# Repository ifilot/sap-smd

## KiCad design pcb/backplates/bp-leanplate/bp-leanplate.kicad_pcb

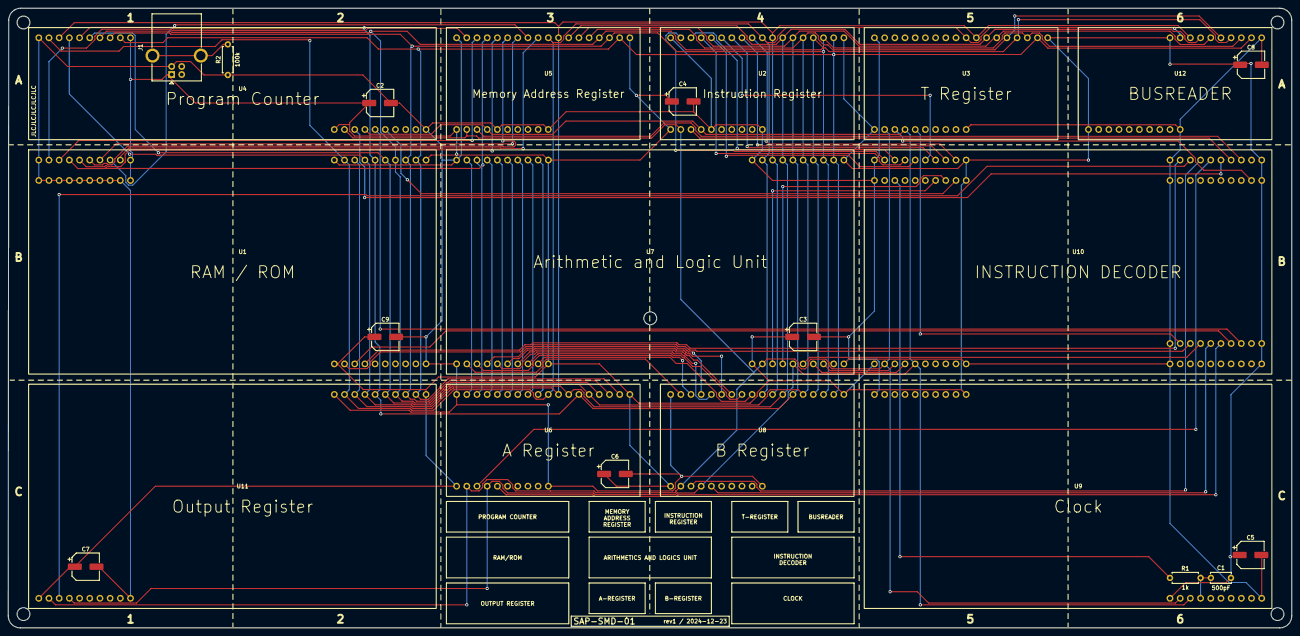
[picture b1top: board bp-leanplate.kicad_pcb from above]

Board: 2 copper layers, 319.9 x 154.4 mm, 29 parts (0 on the bottom side), 67 nets.

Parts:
C1: 500pF; C_Disc_D5.0mm_W2.5mm_P5.00mm
C2: 10uF; CP_Elec_6.3x3.9
C3, C4, C5, C6, C7, C8, C9: 220uF; CP_Elec_6.3x3.9
H1, H2, H3, H4, H5: MountingHole; MountingHole_3.2mm_M3
J1: USB_B; USB_B_OST_USB-B1HSxx_Horizontal
R1: 1k; R_Axial_DIN0207_L6.3mm_D2.5mm_P7.62mm_Horizontal
R2: 100k; R_Axial_DIN0207_L6.3mm_D2.5mm_P7.62mm_Horizontal
U1: RAM / ROM; sap-ramrom
U2: Instruction Register; sap-gpr-halfsize
U3: T Register; sap-gpr-halfsize
U4: Program Counter; sap-pc
U5: Memory Address Register; sap-gpr-halfsize
U6: A Register; sap-gpr-halfsize
U7: Arithmetic and Logic Unit; sap-alu
U8: B Register; sap-gpr-halfsize
U9: Clock; sap-clock
U10: INSTRUCTION DECODER; sap-id
U11: Output Register; sap-output
U12: BUSREADER; sap-busreader

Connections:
AI: U6.19 (IN), U10.13 (OCRA4)
AO: U6.21 (OUT), U10.28 (OCRB3)
A_D0: U6.9 (L0), U7.9 (A0)
A_D1: U6.10 (L1), U7.10 (A1)
A_D2: U6.11 (L2), U7.11 (A2)
A_D3: U6.12 (L3), U7.12 (A3)
A_D4: U6.13 (L4), U7.13 (A4)
A_D5: U6.14 (L5), U7.14 (A5)
A_D6: U6.15 (L6), U7.15 (A6)
A_D7: U6.16 (L7), U7.16 (A7)
BI: U8.19 (IN), U10.14 (OCRA5)
BO: U8.21 (OUT), U10.29 (OCRB4)
BUS0: U1.1 (BUS0), U2.1 (BUS0), U3.1 (BUS0), U4.1 (BUS0), U5.1 (BUS0), U6.1 (BUS0), U7.1 (BUS0), U8.1 (BUS0), U11.1 (BUS0), U12.1 (BUS0)
BUS1: U1.2 (BUS1), U2.2 (BUS1), U3.2 (BUS1), U4.2 (BUS1), U5.2 (BUS1), U6.2 (BUS1), U7.2 (BUS1), U8.2 (BUS1), U11.2 (BUS1), U12.2 (BUS1)
BUS2: U1.3 (BUS2), U2.3 (BUS2), U3.3 (BUS2), U4.3 (BUS2), U5.3 (BUS2), U6.3 (BUS2), U7.3 (BUS2), U8.3 (BUS2), U11.3 (BUS2), U12.3 (BUS2)
BUS3: U1.4 (BUS3), U2.4 (BUS3), U3.4 (BUS3), U4.4 (BUS3), U5.4 (BUS3), U6.4 (BUS3), U7.4 (BUS3), U8.4 (BUS3), U11.4 (BUS3), U12.4 (BUS3)
BUS4: U1.5 (BUS4), U2.5 (BUS4), U3.5 (BUS4), U4.5 (BUS4), U5.5 (BUS4), U6.5 (BUS4), U7.5 (BUS4), U8.5 (BUS4), U11.5 (BUS4), U12.5 (BUS4)
BUS5: U1.6 (BUS5), U2.6 (BUS5), U3.6 (BUS5), U4.6 (BUS5), U5.6 (BUS5), U6.6 (BUS5), U7.6 (BUS5), U8.6 (BUS5), U11.6 (BUS5), U12.6 (BUS5)
BUS6: U1.7 (BUS6), U2.7 (BUS6), U3.7 (BUS6), U4.7 (BUS6), U5.7 (BUS6), U6.7 (BUS6), U7.7 (BUS6), U8.7 (BUS6), U11.7 (BUS6), U12.7 (BUS6)
BUS7: U1.8 (BUS7), U2.8 (BUS7), U3.8 (BUS7), U4.8 (BUS7), U5.8 (BUS7), U6.8 (BUS7), U7.8 (BUS7), U8.8 (BUS7), U11.8 (BUS7), U12.8 (BUS7)
B_D0: U7.17 (B0), U8.9 (L0)
B_D1: U7.18 (B1), U8.10 (L1)
B_D2: U7.19 (B2), U8.11 (L2)
B_D3: U7.20 (B3), U8.12 (L3)
B_D4: U7.21 (B4), U8.13 (L4)
B_D5: U7.22 (B5), U8.14 (L5)
B_D6: U7.23 (B6), U8.15 (L6)
B_D7: U7.24 (B7), U8.16 (L7)
CE: U4.14 (CE), U10.41 (PCL0)
CF: U7.31 (CF), U10.52 (CF)
CLK: U2.18 (CLK), U3.18 (CLK), U4.10 (CLK), U5.18 (CLK), U6.18 (CLK), U7.26 (CLK), U8.18 (CLK), U9.2 (CLK), U10.50 (CLK), U11.10 (CLK)
CO: U4.13 (CO), U10.26 (OCRB1)
EO: U7.30 (EO), U10.30 (OCRB5)
FI: U7.28 (FI), U10.42 (PCL1)
GND: C2.2, C3.2, C4.2, C5.2, C6.2, C7.2, C8.2, C9.2, J1.4 (GND), R2.1, U1.17 (L8), U1.18 (L9), U1.19 (L10), U1.20 (L11), U1.21 (L12), U1.22 (L13), U1.23 (L14), U1.24 (L15), U1.29 (GND), U2.21 (OUT), U2.22 (GND), U3.22 (GND), U4.15 (GND), U5.21 (OUT), U5.22 (GND), U6.22 (GND), U7.33 (GND), U8.22 (GND), U9.5 (GND), U10.54 (GND), U11.13 (GND), U12.10 (GND)
HLT: R1.1, U10.47 (PCL6)
HLTIN: C1.1, R1.2, U9.4 (HLT)
II: U2.19 (IN), U10.11 (OCRA2)
IR_D0: U2.9 (L0), U10.1 (I0)
IR_D1: U2.10 (L1), U10.2 (I1)
IR_D2: U2.11 (L2), U10.3 (I2)
IR_D3: U2.12 (L3), U10.4 (I3)
IR_D4: U2.13 (L4), U10.5 (I4)
IR_D5: U2.14 (L5), U10.6 (I5)
IR_D6: U2.15 (L6), U10.7 (I6)
IR_D7: U2.16 (L7), U10.8 (I7)
J: U4.11 (J), U10.12 (OCRA3)
MAR_A0: U1.9 (L0), U5.9 (L0)
MAR_A1: U1.10 (L1), U5.10 (L1)
MAR_A2: U1.11 (L2), U5.11 (L2)
MAR_A3: U1.12 (L3), U5.12 (L3)
MAR_A4: U1.13 (L4), U5.13 (L4)
MAR_A5: U1.14 (L5), U5.14 (L5)
MAR_A6: U1.15 (L6), U5.15 (L6)
MAR_A7: U1.16 (L7), U5.16 (L7)
MI: U5.19 (IN), U10.10 (OCRA1)
unnamed: J1.5 (Shield), R2.2
OI: U10.15 (OCRA6), U11.11 (IN)
PCL2: U7.27 (SU), U10.43 (PCL2)
RI: U1.28 (RI), U10.16 (OCRA7)
RO: U1.26 (RO), U10.31 (OCRB6)
RRO: U1.27 (RRO), U10.27 (OCRB2)
TI: U3.19 (IN), U10.17 (OCRA8)
TO: U3.21 (OUT), U10.32 (OCRB7)
VCC: C1.2, C2.1, C3.1, C4.1, C5.1, C6.1, C7.1, C8.1, C9.1, J1.1 (VBUS), U1.25 (VCC), U2.17 (VCC), U3.17 (VCC), U4.9 (VCC), U5.17 (VCC), U6.17 (VCC), U7.25 (VCC), U8.17 (VCC), U9.1 (VCC), U10.49 (VCC), U11.9 (VCC), U12.9 (VCC)
ZF: U7.32 (ZF), U10.51 (ZF)
~CLR: U2.20 (~CLR), U3.20 (~CLR), U4.12 (~CLR), U5.20 (~CLR), U6.20 (~CLR), U7.29 (CLR), U8.20 (~CLR), U9.3 (~CLR), U10.53 (~CLR), U11.12 (~CLR)

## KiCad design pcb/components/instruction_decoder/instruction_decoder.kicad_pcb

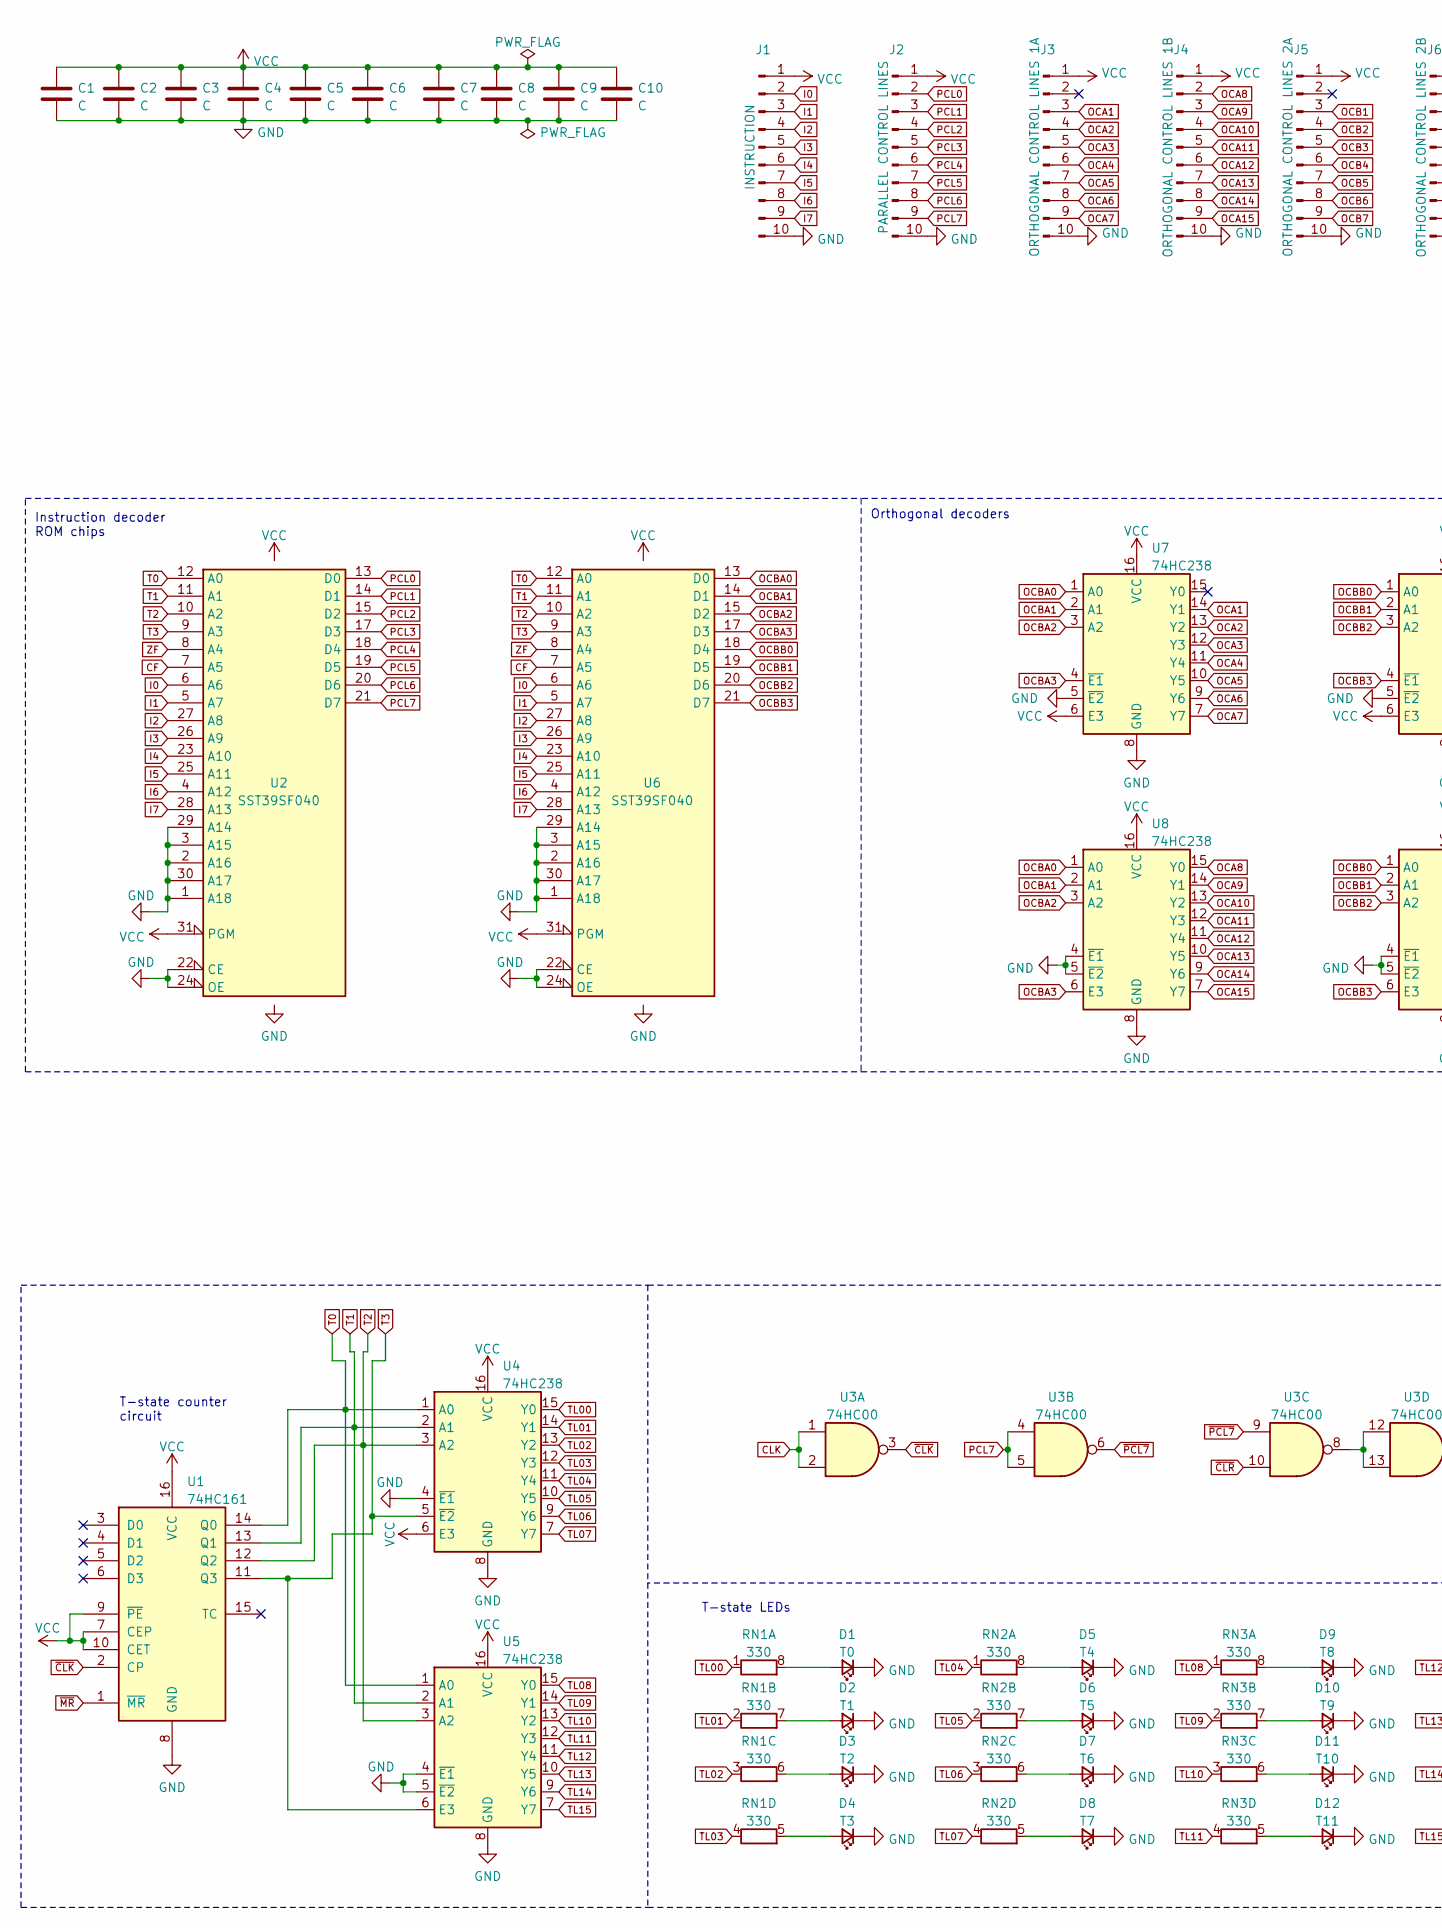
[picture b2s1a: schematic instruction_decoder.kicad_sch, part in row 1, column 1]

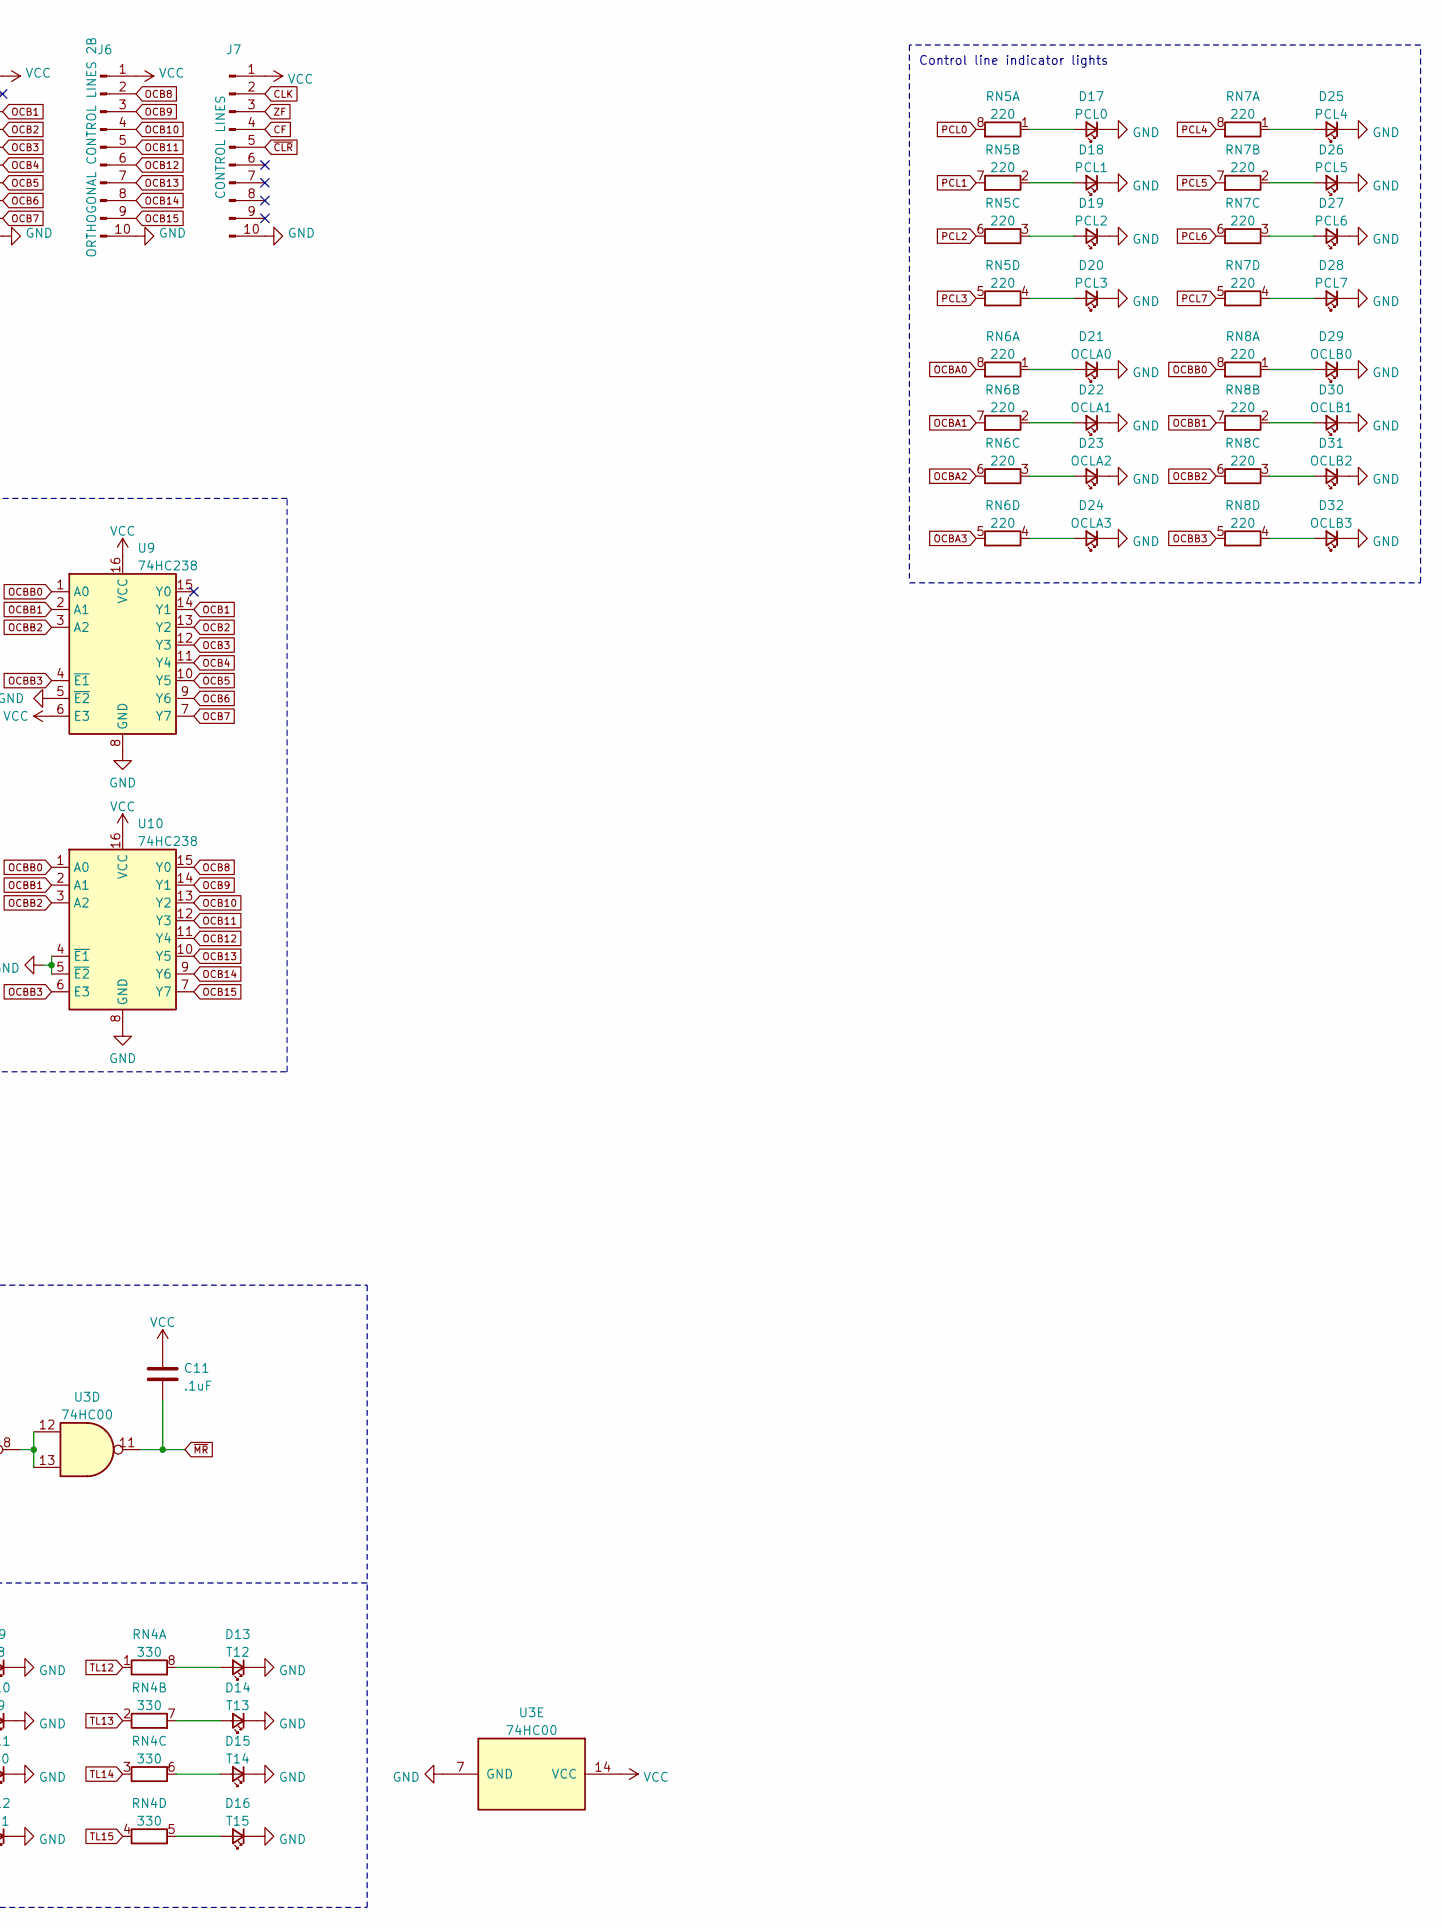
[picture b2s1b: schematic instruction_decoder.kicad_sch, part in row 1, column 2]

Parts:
C1, C2, C3, C4, C5, C6, C7, C8, C9, C10: C; C_0805_2012Metric
C11: .1uF; C_Disc_D5.0mm_W2.5mm_P5.00mm
D1: T0; LED_0805_2012Metric
D2: T1; LED_0805_2012Metric
D3: T2; LED_0805_2012Metric
D4: T3; LED_0805_2012Metric
D5: T4; LED_0805_2012Metric
D6: T5; LED_0805_2012Metric
D7: T6; LED_0805_2012Metric
D8: T7; LED_0805_2012Metric
D9: T8; LED_0805_2012Metric
D10: T9; LED_0805_2012Metric
D11: T10; LED_0805_2012Metric
D12: T11; LED_0805_2012Metric
D13: T12; LED_0805_2012Metric
D14: T13; LED_0805_2012Metric
D15: T14; LED_0805_2012Metric
D16: T15; LED_0805_2012Metric
D17: PCL0; LED_0805_2012Metric
D18: PCL1; LED_0805_2012Metric
D19: PCL2; LED_0805_2012Metric
D20: PCL3; LED_0805_2012Metric
D21: OCLA0; LED_0805_2012Metric
D22: OCLA1; LED_0805_2012Metric
D23: OCLA2; LED_0805_2012Metric
D24: OCLA3; LED_0805_2012Metric
D25: PCL4; LED_0805_2012Metric
D26: PCL5; LED_0805_2012Metric
D27: PCL6; LED_0805_2012Metric
D28: PCL7; LED_0805_2012Metric
D29: OCLB0; LED_0805_2012Metric
D30: OCLB1; LED_0805_2012Metric
D31: OCLB2; LED_0805_2012Metric
D32: OCLB3; LED_0805_2012Metric
J1: INSTRUCTION; PinHeader_1x10_P2.54mm_Vertical
J2: PARALLEL CONTROL LINES; PinHeader_1x10_P2.54mm_Vertical
J3: ORTHOGONAL CONTROL LINES 1A; PinHeader_1x10_P2.54mm_Vertical
J4: ORTHOGONAL CONTROL LINES 1B; PinHeader_1x10_P2.54mm_Vertical
J5: ORTHOGONAL CONTROL LINES 2A; PinHeader_1x10_P2.54mm_Vertical
J6: ORTHOGONAL CONTROL LINES 2B; PinHeader_1x10_P2.54mm_Vertical
J7: CONTROL LINES; PinHeader_1x10_P2.54mm_Vertical
RN1, RN2, RN3, RN4: 330; R_Array_Convex_4x0603
RN5, RN6, RN7, RN8: 220; R_Array_Convex_4x0603
U1: 74HC161; SO-16_3.9x9.9mm_P1.27mm
U2, U6: SST39SF040; PLCC-32_THT-Socket
U3: 74HC00; SO-14_3.9x8.65mm_P1.27mm
U4, U5, U7, U8, U9, U10: 74HC238; SO-16_3.9x9.9mm_P1.27mm

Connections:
CF: J7.4, U2.7 (A5), U6.7 (A5)
CLK: J7.2, U3.1, U3.2
GND: C1.2, C2.2, C3.2, C4.2, C5.2, C6.2, C7.2, C8.2, C9.2, C10.2, D1.1 (K), D2.1 (K), D3.1 (K), D4.1 (K), D5.1 (K), D6.1 (K), D7.1 (K), D8.1 (K), D9.1 (K), D10.1 (K), D11.1 (K), D12.1 (K), D13.1 (K), D14.1 (K), D15.1 (K), D16.1 (K), D17.1 (K), D18.1 (K), D19.1 (K), D20.1 (K), D21.1 (K), D22.1 (K), D23.1 (K), D24.1 (K), D25.1 (K), D26.1 (K), D27.1 (K), D28.1 (K), D29.1 (K), D30.1 (K), D31.1 (K), D32.1 (K), J1.10, J2.10, J3.10, J4.10, J5.10, J6.10, J7.10, U1.8 (GND), U2.1 (A18), U2.2 (A16), U2.3 (A15), U2.16 (GND), U2.22 (CE), U2.24 (OE), U2.29 (A14), U2.30 (A17), U3.7 (GND), U4.4 (~E1), U4.8 (GND), U5.4 (~E1), U5.5 (~E2), U5.8 (GND), U6.1 (A18), U6.2 (A16), U6.3 (A15), U6.16 (GND), U6.22 (CE), U6.24 (OE), U6.29 (A14), U6.30 (A17), U7.5 (~E2), U7.8 (GND), U8.4 (~E1), U8.5 (~E2), U8.8 (GND), U9.5 (~E2), U9.8 (GND), U10.4 (~E1), U10.5 (~E2), U10.8 (GND)
I0: J1.2, U2.6 (A6), U6.6 (A6)
I1: J1.3, U2.5 (A7), U6.5 (A7)
I2: J1.4, U2.27 (A8), U6.27 (A8)
I3: J1.5, U2.26 (A9), U6.26 (A9)
I4: J1.6, U2.23 (A10), U6.23 (A10)
I5: J1.7, U2.25 (A11), U6.25 (A11)
I6: J1.8, U2.4 (A12), U6.4 (A12)
I7: J1.9, U2.28 (A13), U6.28 (A13)
unnamed: D1.2 (A), RN1.8 (R1.2)
unnamed: D2.2 (A), RN1.7 (R2.2)
unnamed: D3.2 (A), RN1.6 (R3.2)
unnamed: D4.2 (A), RN1.5 (R4.2)
unnamed: D5.2 (A), RN2.8 (R1.2)
unnamed: D6.2 (A), RN2.7 (R2.2)
unnamed: D7.2 (A), RN2.6 (R3.2)
unnamed: D8.2 (A), RN2.5 (R4.2)
unnamed: D9.2 (A), RN3.8 (R1.2)
unnamed: D10.2 (A), RN3.7 (R2.2)
unnamed: D11.2 (A), RN3.6 (R3.2)
unnamed: D12.2 (A), RN3.5 (R4.2)
unnamed: D13.2 (A), RN4.8 (R1.2)
unnamed: D14.2 (A), RN4.7 (R2.2)
unnamed: D15.2 (A), RN4.6 (R3.2)
unnamed: D16.2 (A), RN4.5 (R4.2)
unnamed: D17.2 (A), RN5.1 (R1.1)
unnamed: D18.2 (A), RN5.2 (R2.1)
unnamed: D19.2 (A), RN5.3 (R3.1)
unnamed: D20.2 (A), RN5.4 (R4.1)
unnamed: D21.2 (A), RN6.1 (R1.1)
unnamed: D22.2 (A), RN6.2 (R2.1)
unnamed: D23.2 (A), RN6.3 (R3.1)
unnamed: D24.2 (A), RN6.4 (R4.1)
unnamed: D25.2 (A), RN7.1 (R1.1)
unnamed: D26.2 (A), RN7.2 (R2.1)
unnamed: D27.2 (A), RN7.3 (R3.1)
unnamed: D28.2 (A), RN7.4 (R4.1)
unnamed: D29.2 (A), RN8.1 (R1.1)
unnamed: D30.2 (A), RN8.2 (R2.1)
unnamed: D31.2 (A), RN8.3 (R3.1)
unnamed: D32.2 (A), RN8.4 (R4.1)
unnamed: U3.8, U3.12, U3.13
OCA1: J3.3, U7.14 (Y1)
OCA2: J3.4, U7.13 (Y2)
OCA3: J3.5, U7.12 (Y3)
OCA4: J3.6, U7.11 (Y4)
OCA5: J3.7, U7.10 (Y5)
OCA6: J3.8, U7.9 (Y6)
OCA7: J3.9, U7.7 (Y7)
OCA8: J4.2, U8.15 (Y0)
OCA9: J4.3, U8.14 (Y1)
OCA10: J4.4, U8.13 (Y2)
OCA11: J4.5, U8.12 (Y3)
OCA12: J4.6, U8.11 (Y4)
OCA13: J4.7, U8.10 (Y5)
OCA14: J4.8, U8.9 (Y6)
OCA15: J4.9, U8.7 (Y7)
OCB1: J5.3, U9.14 (Y1)
OCB2: J5.4, U9.13 (Y2)
OCB3: J5.5, U9.12 (Y3)
OCB4: J5.6, U9.11 (Y4)
OCB5: J5.7, U9.10 (Y5)
OCB6: J5.8, U9.9 (Y6)
OCB7: J5.9, U9.7 (Y7)
OCB8: J6.2, U10.15 (Y0)
OCB9: J6.3, U10.14 (Y1)
OCB10: J6.4, U10.13 (Y2)
OCB11: J6.5, U10.12 (Y3)
OCB12: J6.6, U10.11 (Y4)
OCB13: J6.7, U10.10 (Y5)
OCB14: J6.8, U10.9 (Y6)
OCB15: J6.9, U10.7 (Y7)
OCBA0: RN6.8 (R1.2), U6.13 (D0), U7.1 (A0), U8.1 (A0)
OCBA1: RN6.7 (R2.2), U6.14 (D1), U7.2 (A1), U8.2 (A1)
OCBA2: RN6.6 (R3.2), U6.15 (D2), U7.3 (A2), U8.3 (A2)
OCBA3: RN6.5 (R4.2), U6.17 (D3), U7.4 (~E1), U8.6 (E3)
OCBB0: RN8.8 (R1.2), U6.18 (D4), U9.1 (A0), U10.1 (A0)
OCBB1: RN8.7 (R2.2), U6.19 (D5), U9.2 (A1), U10.2 (A1)
OCBB2: RN8.6 (R3.2), U6.20 (D6), U9.3 (A2), U10.3 (A2)
OCBB3: RN8.5 (R4.2), U6.21 (D7), U9.4 (~E1), U10.6 (E3)
PCL0: J2.2, RN5.8 (R1.2), U2.13 (D0)
PCL1: J2.3, RN5.7 (R2.2), U2.14 (D1)
PCL2: J2.4, RN5.6 (R3.2), U2.15 (D2)
PCL3: J2.5, RN5.5 (R4.2), U2.17 (D3)
PCL4: J2.6, RN7.8 (R1.2), U2.18 (D4)
PCL5: J2.7, RN7.7 (R2.2), U2.19 (D5)
PCL6: J2.8, RN7.6 (R3.2), U2.20 (D6)
PCL7: J2.9, RN7.5 (R4.2), U2.21 (D7), U3.4, U3.5
T0: U1.14 (Q0), U2.12 (A0), U4.1 (A0), U5.1 (A0), U6.12 (A0)
T1: U1.13 (Q1), U2.11 (A1), U4.2 (A1), U5.2 (A1), U6.11 (A1)
T2: U1.12 (Q2), U2.10 (A2), U4.3 (A2), U5.3 (A2), U6.10 (A2)
T3: U1.11 (Q3), U2.9 (A3), U4.5 (~E2), U5.6 (E3), U6.9 (A3)
TL00: RN1.1 (R1.1), U4.15 (Y0)
TL01: RN1.2 (R2.1), U4.14 (Y1)
TL02: RN1.3 (R3.1), U4.13 (Y2)
TL03: RN1.4 (R4.1), U4.12 (Y3)
TL04: RN2.1 (R1.1), U4.11 (Y4)
TL05: RN2.2 (R2.1), U4.10 (Y5)
TL06: RN2.3 (R3.1), U4.9 (Y6)
TL07: RN2.4 (R4.1), U4.7 (Y7)
TL08: RN3.1 (R1.1), U5.15 (Y0)
TL09: RN3.2 (R2.1), U5.14 (Y1)
TL10: RN3.3 (R3.1), U5.13 (Y2)
TL11: RN3.4 (R4.1), U5.12 (Y3)
TL12: RN4.1 (R1.1), U5.11 (Y4)
TL13: RN4.2 (R2.1), U5.10 (Y5)
TL14: RN4.3 (R3.1), U5.9 (Y6)
TL15: RN4.4 (R4.1), U5.7 (Y7)
VCC: C1.1, C2.1, C3.1, C4.1, C5.1, C6.1, C7.1, C8.1, C9.1, C10.1, C11.1, J1.1, J2.1, J3.1, J4.1, J5.1, J6.1, J7.1, U1.7 (CEP), U1.9 (~PE), U1.10 (CET), U1.16 (VCC), U2.31 (PGM), U2.32 (VCC), U3.14 (VCC), U4.6 (E3), U4.16 (VCC), U5.16 (VCC), U6.31 (PGM), U6.32 (VCC), U7.6 (E3), U7.16 (VCC), U8.16 (VCC), U9.6 (E3), U9.16 (VCC), U10.16 (VCC)
ZF: J7.3, U2.8 (A4), U6.8 (A4)
~CLK: U1.2 (CP), U3.3
~CLR: J7.5, U3.10
~MR: C11.2, U1.1 (~MR), U3.11
~PCL7: U3.6, U3.9

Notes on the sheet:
T-state counter circuit
Orthogonal decoders
T-state LEDs
Instruction decoder ROM chips
Control line indicator lights

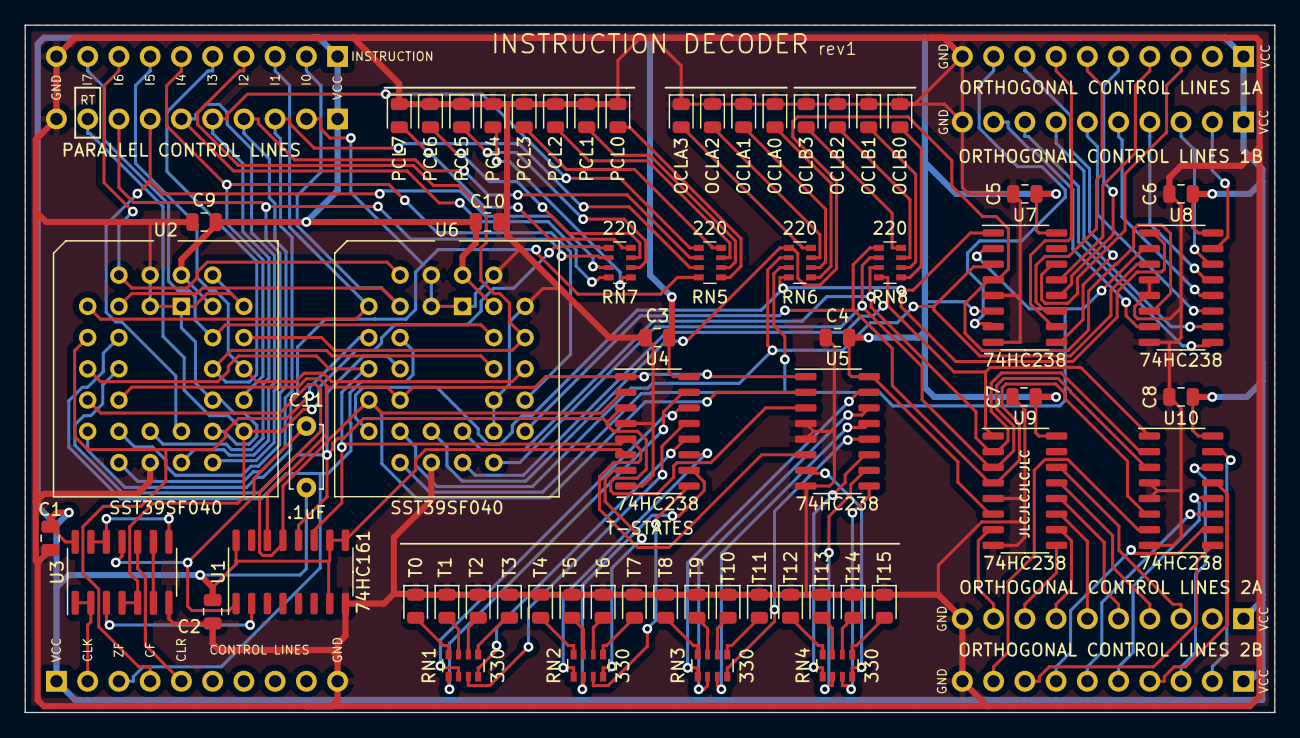
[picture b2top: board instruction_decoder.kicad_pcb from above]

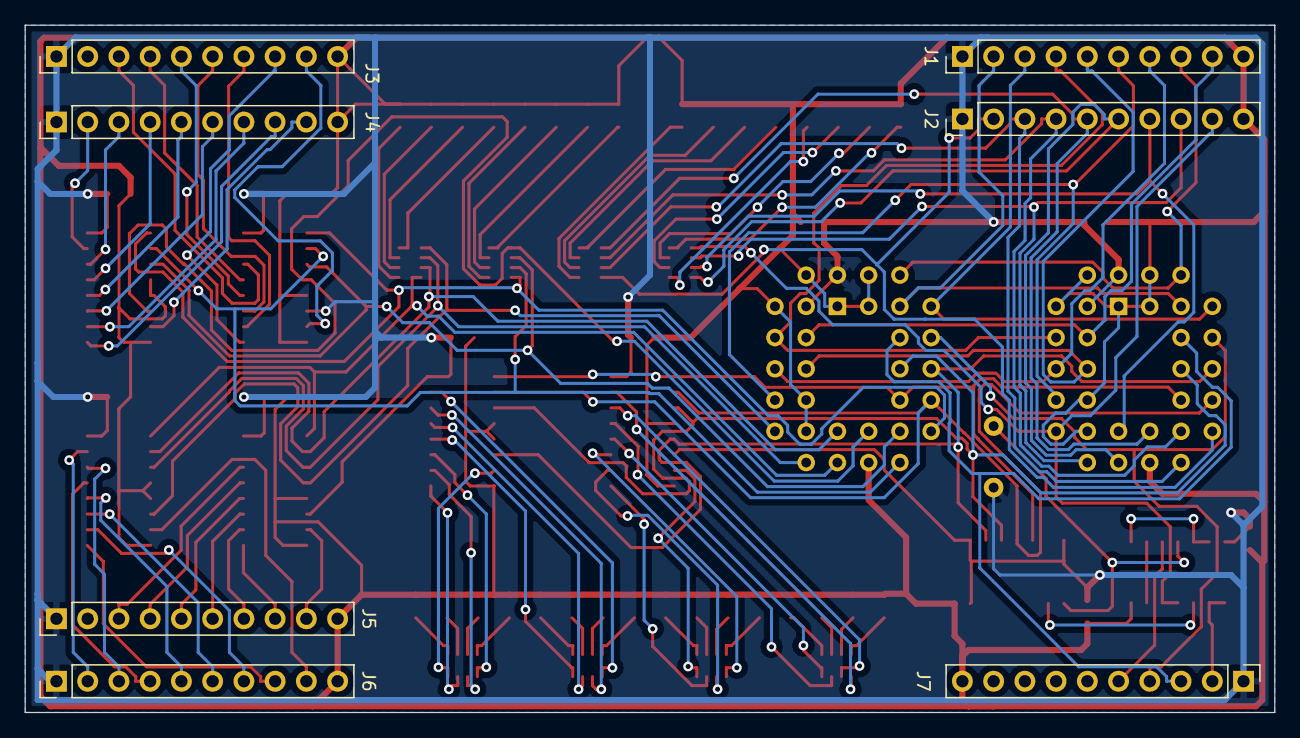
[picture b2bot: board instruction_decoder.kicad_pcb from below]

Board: 2 copper layers, 101.6 x 55.9 mm, 68 parts (7 on the bottom side), 116 nets.

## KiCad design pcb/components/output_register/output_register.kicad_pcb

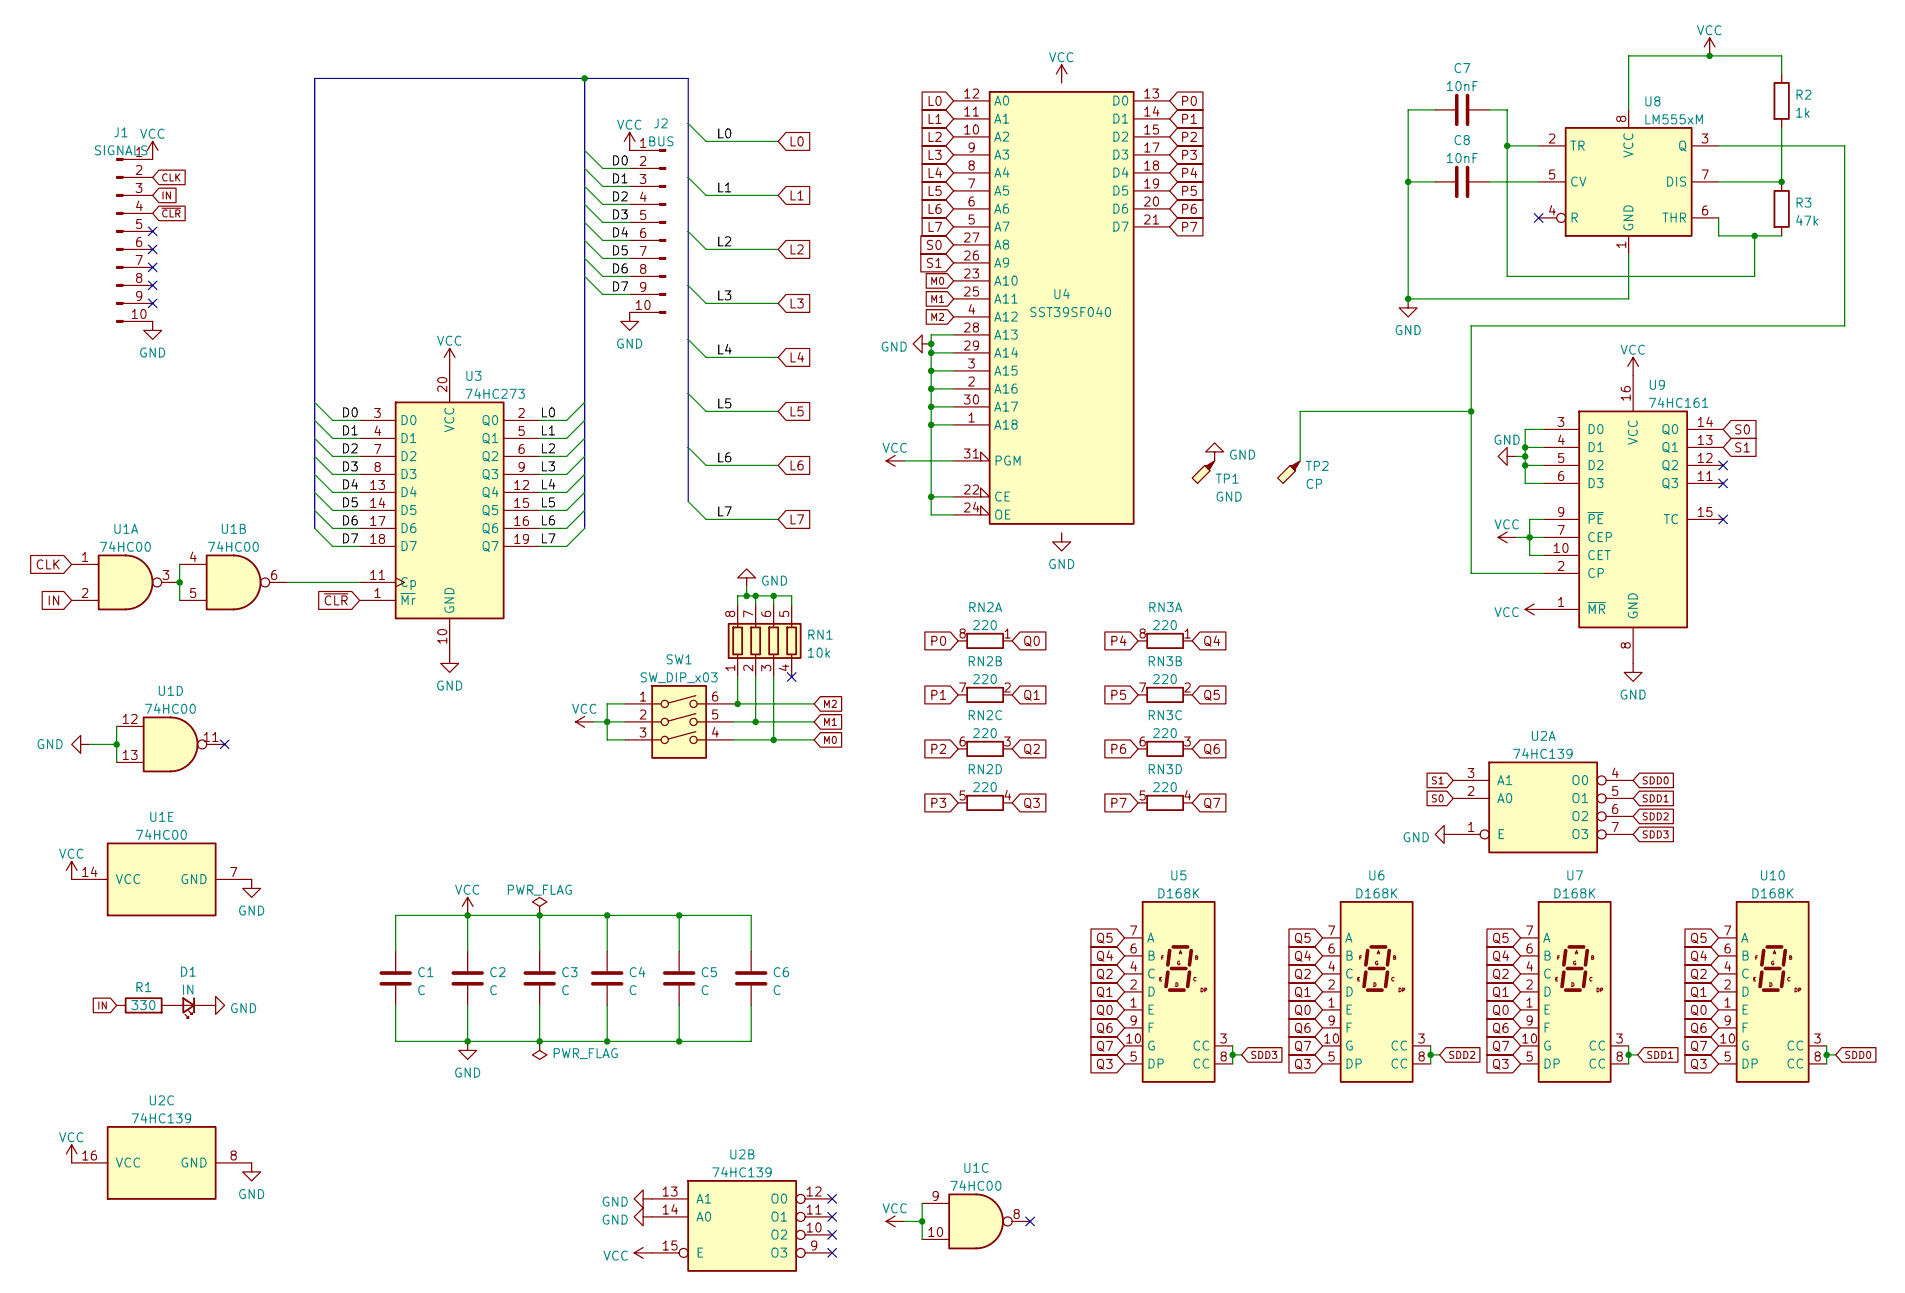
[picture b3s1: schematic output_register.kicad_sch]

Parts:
C1, C2, C3, C4, C5, C6: C; C_0805_2012Metric
C7, C8: 10nF; C_0805_2012Metric
D1: IN; LED_0805_2012Metric
J1: SIGNALS; PinHeader_1x10_P2.54mm_Vertical
J2: BUS; PinHeader_1x10_P2.54mm_Vertical
R1: 330; R_0805_2012Metric
R2: 1k; R_0805_2012Metric
R3: 47k; R_0805_2012Metric
RN1: 10k; R_Array_Convex_4x0603
RN2, RN3: 220; R_Array_Convex_4x0603
SW1: SW_DIP_x03; SW_DIP_SPSTx03_Slide_9.78x9.8mm_W7.62mm_P2.54mm
TP1: GND; TestPoint_THTPad_D2.0mm_Drill1.0mm
TP2: CP; TestPoint_THTPad_D2.0mm_Drill1.0mm
U1: 74HC00; SO-14_3.9x8.65mm_P1.27mm
U2: 74HC139; SO-16_3.9x9.9mm_P1.27mm
U3: 74HC273; SOIC-20W_7.5x12.8mm_P1.27mm
U4: SST39SF040; PLCC-32_THT-Socket
U5, U6, U7, U10: D168K; D1X8K
U8: LM555xM; SOIC-8_3.9x4.9mm_P1.27mm
U9: 74HC161; SO-16_3.9x9.9mm_P1.27mm

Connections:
/D0: J2.2, U3.3 (D0)
/D1: J2.3, U3.4 (D1)
/D2: J2.4, U3.7 (D2)
/D3: J2.5, U3.8 (D3)
/D4: J2.6, U3.13 (D4)
/D5: J2.7, U3.14 (D5)
/D6: J2.8, U3.17 (D6)
/D7: J2.9, U3.18 (D7)
CLK: J1.2, U1.1
GND: C1.2, C2.2, C3.2, C4.2, C5.2, C6.2, C7.1, C8.1, D1.1 (K), J1.10, J2.10, RN1.5 (R4.2), RN1.6 (R3.2), RN1.7 (R2.2), RN1.8 (R1.2), TP1.1, U1.7 (GND), U1.12, U1.13, U2.1 (E), U2.8 (GND), U2.13 (A1), U2.14 (A0), U3.10 (GND), U4.1 (A18), U4.2 (A16), U4.3 (A15), U4.16 (GND), U4.22 (CE), U4.24 (OE), U4.28 (A13), U4.29 (A14), U4.30 (A17), U8.1 (GND), U9.3 (D0), U9.4 (D1), U9.5 (D2), U9.6 (D3), U9.8 (GND)
IN: J1.3, R1.1, U1.2
L0: U3.2 (Q0), U4.12 (A0)
L1: U3.5 (Q1), U4.11 (A1)
L2: U3.6 (Q2), U4.10 (A2)
L3: U3.9 (Q3), U4.9 (A3)
L4: U3.12 (Q4), U4.8 (A4)
L5: U3.15 (Q5), U4.7 (A5)
L6: U3.16 (Q6), U4.6 (A6)
L7: U3.19 (Q7), U4.5 (A7)
M0: RN1.3 (R3.1), SW1.4, U4.23 (A10)
M1: RN1.2 (R2.1), SW1.5, U4.25 (A11)
M2: RN1.1 (R1.1), SW1.6, U4.4 (A12)
unnamed: C7.2, R3.2, U8.2 (TR), U8.6 (THR)
unnamed: C8.2, U8.5 (CV)
unnamed: D1.2 (A), R1.2
unnamed: R2.2, R3.1, U8.7 (DIS)
unnamed: U1.3, U1.4, U1.5
unnamed: U1.6, U3.11 (Cp)
unnamed: TP2.1, U8.3 (Q), U9.2 (CP)
P0: RN2.8 (R1.2), U4.13 (D0)
P1: RN2.7 (R2.2), U4.14 (D1)
P2: RN2.6 (R3.2), U4.15 (D2)
P3: RN2.5 (R4.2), U4.17 (D3)
P4: RN3.8 (R1.2), U4.18 (D4)
P5: RN3.7 (R2.2), U4.19 (D5)
P6: RN3.6 (R3.2), U4.20 (D6)
P7: RN3.5 (R4.2), U4.21 (D7)
Q0: RN2.1 (R1.1), U5.1 (E), U6.1 (E), U7.1 (E), U10.1 (E)
Q1: RN2.2 (R2.1), U5.2 (D), U6.2 (D), U7.2 (D), U10.2 (D)
Q2: RN2.3 (R3.1), U5.4 (C), U6.4 (C), U7.4 (C), U10.4 (C)
Q3: RN2.4 (R4.1), U5.5 (DP), U6.5 (DP), U7.5 (DP), U10.5 (DP)
Q4: RN3.1 (R1.1), U5.6 (B), U6.6 (B), U7.6 (B), U10.6 (B)
Q5: RN3.2 (R2.1), U5.7 (A), U6.7 (A), U7.7 (A), U10.7 (A)
Q6: RN3.3 (R3.1), U5.9 (F), U6.9 (F), U7.9 (F), U10.9 (F)
Q7: RN3.4 (R4.1), U5.10 (G), U6.10 (G), U7.10 (G), U10.10 (G)
S0: U2.2 (A0), U4.27 (A8), U9.14 (Q0)
S1: U2.3 (A1), U4.26 (A9), U9.13 (Q1)
SDD0: U2.4 (O0), U10.3 (CC), U10.8 (CC)
SDD1: U2.5 (O1), U7.3 (CC), U7.8 (CC)
SDD2: U2.6 (O2), U6.3 (CC), U6.8 (CC)
SDD3: U2.7 (O3), U5.3 (CC), U5.8 (CC)
VCC: C1.1, C2.1, C3.1, C4.1, C5.1, C6.1, J1.1, J2.1, R2.1, SW1.1, SW1.2, SW1.3, U1.9, U1.10, U1.14 (VCC), U2.15 (E), U2.16 (VCC), U3.20 (VCC), U4.31 (PGM), U4.32 (VCC), U8.8 (VCC), U9.1 (~MR), U9.7 (CEP), U9.9 (~PE), U9.10 (CET), U9.16 (VCC)
~CLR: J1.4, U3.1 (~Mr)

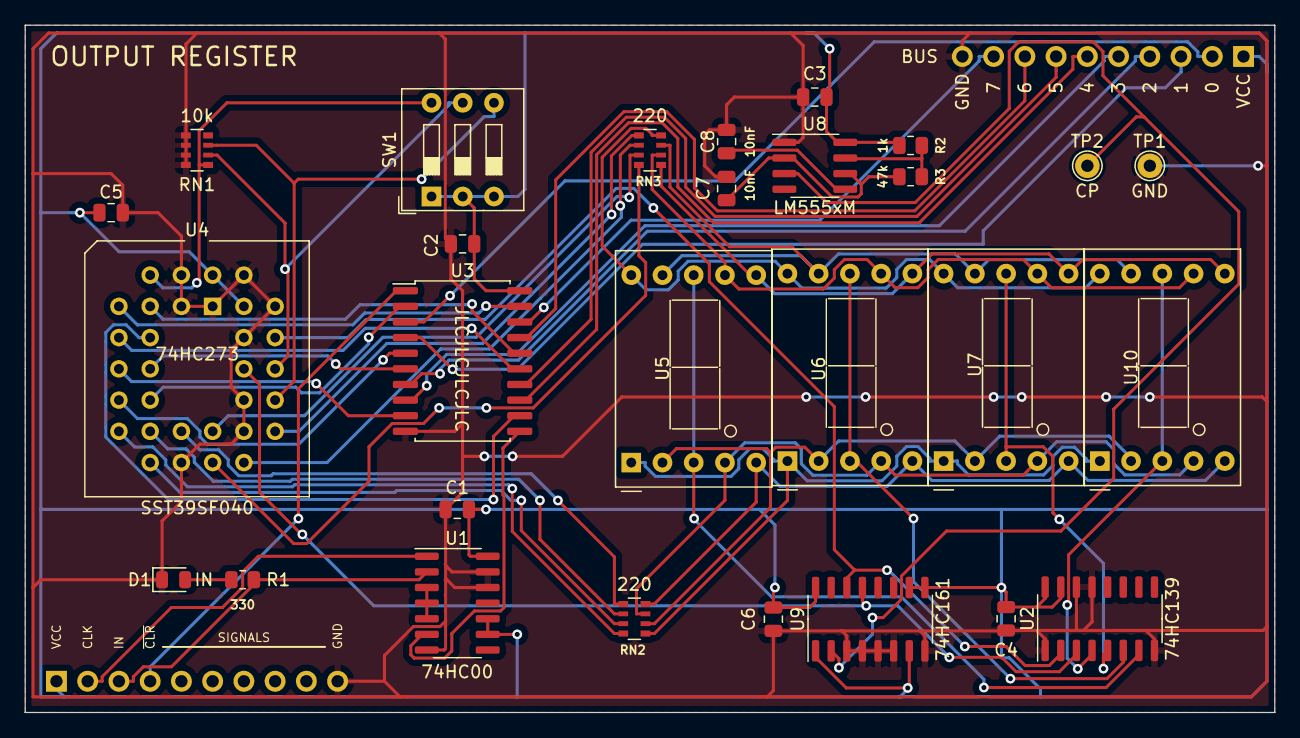
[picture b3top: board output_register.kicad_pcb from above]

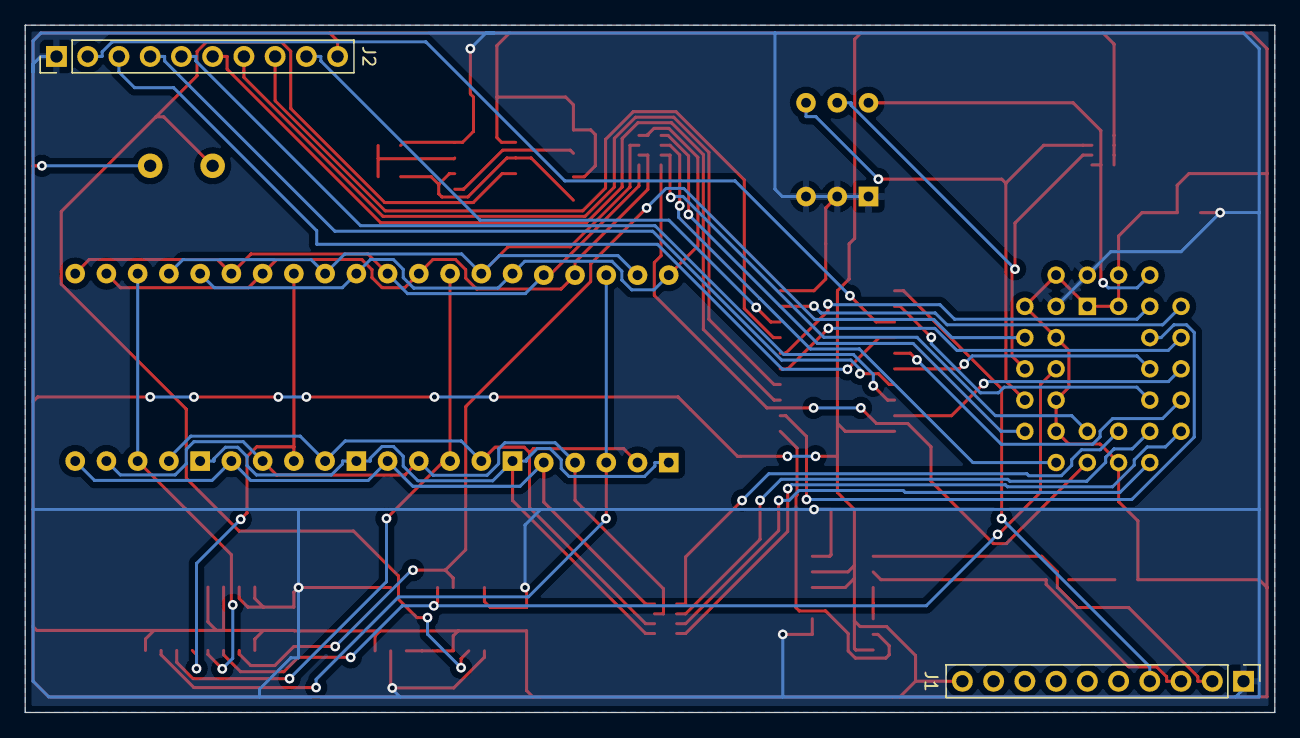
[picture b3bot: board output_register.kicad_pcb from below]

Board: 2 copper layers, 101.6 x 55.9 mm, 30 parts (2 on the bottom side), 53 nets.
